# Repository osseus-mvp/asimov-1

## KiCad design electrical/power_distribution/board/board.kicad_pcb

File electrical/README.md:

## RPU 
> WIP

## Wiring

 was utilised for representing the wiring harness of the robot. 

Please refer to WireViz documentation for available visualisation options.
### Cable Naming Convention

```
W-<ID>-<TYPE>
ID = unique ID
TYPE = Power (PWR) or Signal (SIG) cable bundle
```

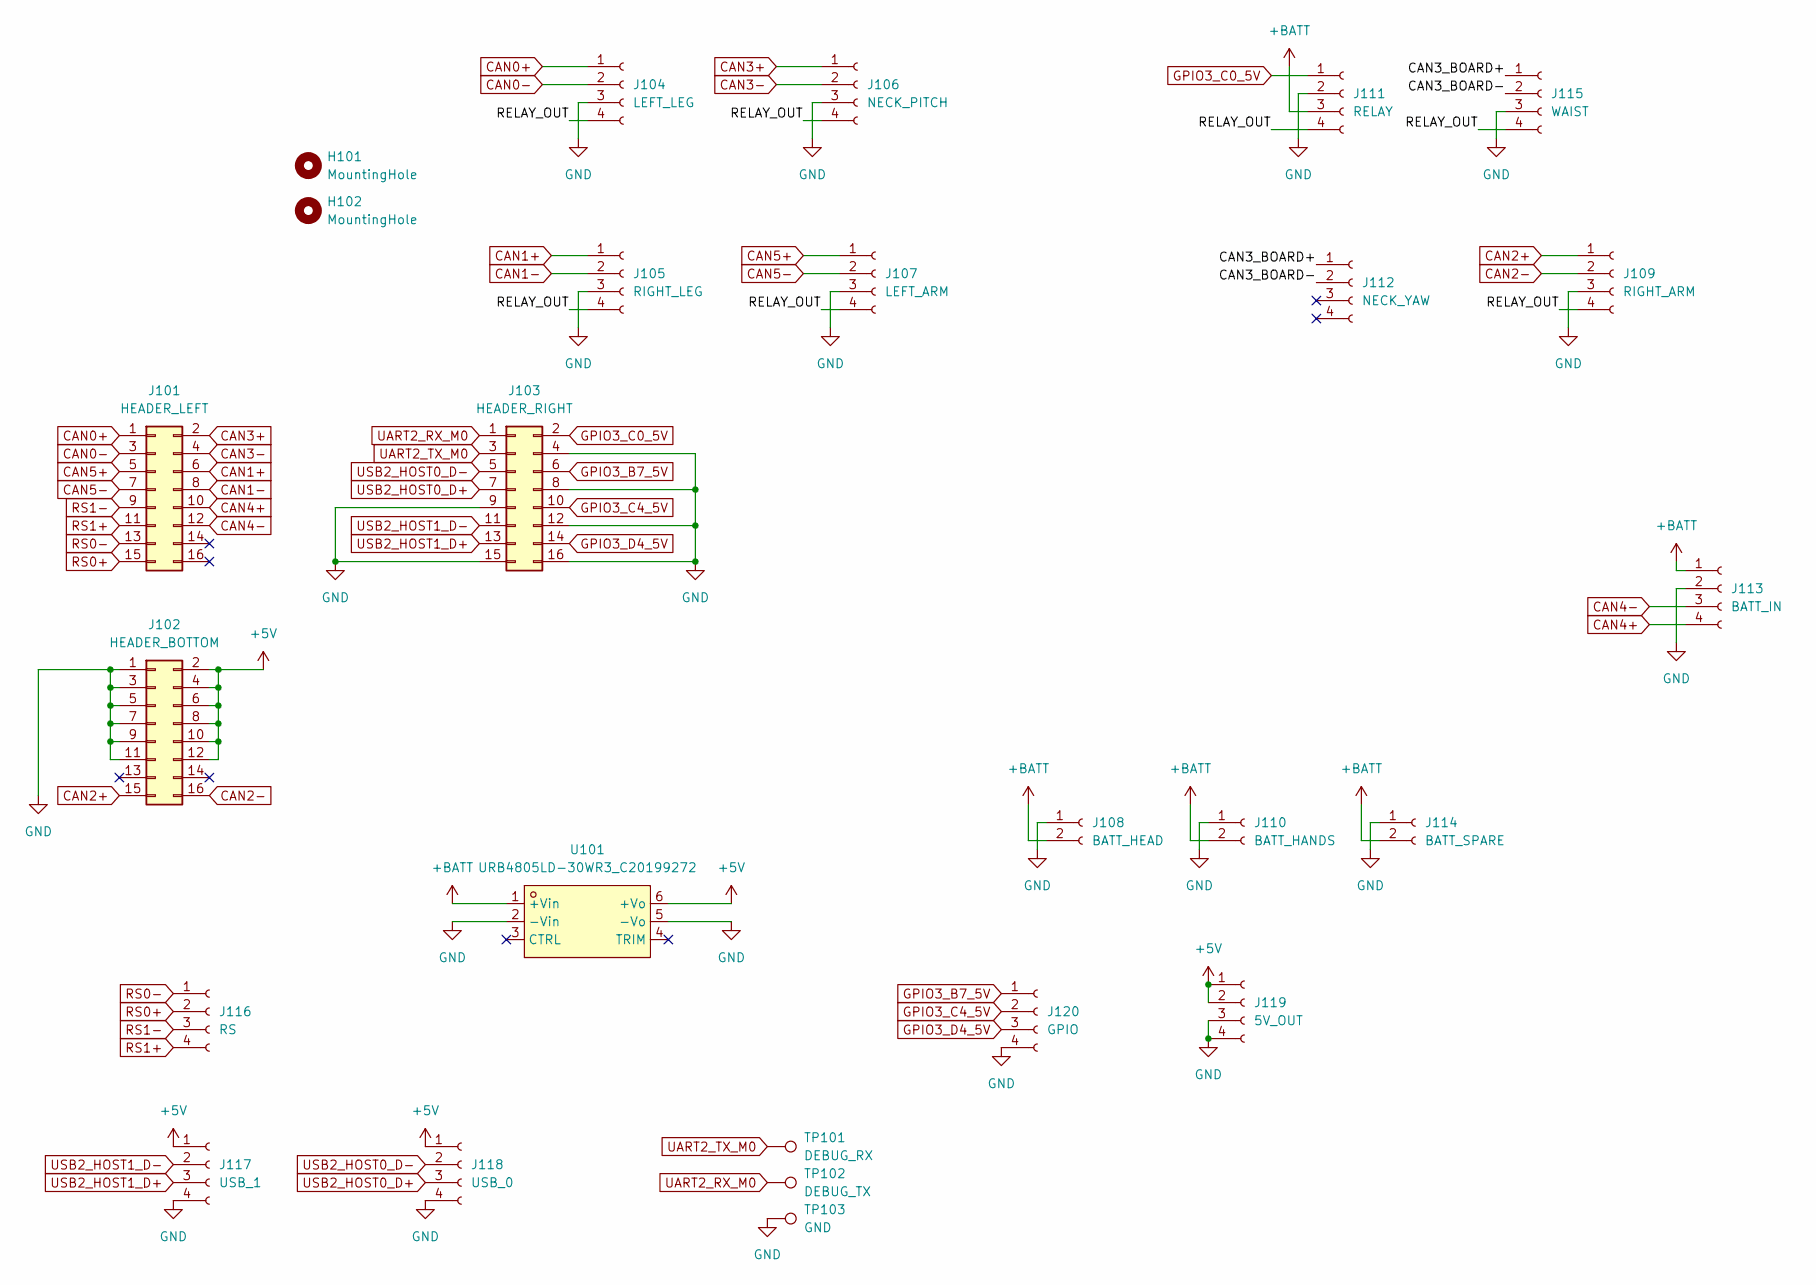
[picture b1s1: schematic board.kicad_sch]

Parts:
H101, H102: MountingHole; MountingHole_4.3mm_M4
J101: HEADER_LEFT; PinSocket_2x08_P2.54mm_Vertical; LCSC C30734
J102: HEADER_BOTTOM; PinSocket_2x08_P2.54mm_Vertical; LCSC C30734
J103: HEADER_RIGHT; PinSocket_2x08_P2.54mm_Vertical; LCSC C30734
J104: LEFT_LEG; CONN-TH_XT30PB-M
J105: RIGHT_LEG; CONN-TH_XT30PB-M
J106: NECK_PITCH; CONN-TH_XT30PB-M
J107: LEFT_ARM; CONN-TH_XT30PB-M
J108: BATT_HEAD; AMASS_XT30UPB-F_1x02_P5.0mm_Vertical; LCSC C108769
J109: RIGHT_ARM; CONN-TH_XT30PB-M
J110: BATT_HANDS; AMASS_XT30UPB-F_1x02_P5.0mm_Vertical; LCSC C108769
J111: RELAY; CONN-TH_XT30PB-M
J112: NECK_YAW; CONN-TH_XT30PB-M
J113: BATT_IN; CONN-SMD_XT90-2-2-PB-MGY; LCSC C19268046
J114: BATT_SPARE; AMASS_XT30UPB-F_1x02_P5.0mm_Vertical; LCSC C108769
J115: WAIST; CONN-TH_XT30PB-M
J116: RS; JST_XH_B4B-XH-A_1x04_P2.50mm_Vertical; LCSC C144395
J117: USB_1; JST_XH_B4B-XH-A_1x04_P2.50mm_Vertical; LCSC C144395
J118: USB_0; JST_XH_B4B-XH-A_1x04_P2.50mm_Vertical; LCSC C144395
J119: 5V_OUT; JST_XH_B4B-XH-A_1x04_P2.50mm_Vertical; LCSC C144395
J120: GPIO; JST_XH_B4B-XH-A_1x04_P2.50mm_Vertical; LCSC C144395
TP101: DEBUG_RX; TestPoint_Pad_D1.0mm
TP102: DEBUG_TX; TestPoint_Pad_D1.0mm
TP103: GND; TestPoint_Pad_D1.0mm
U101: URB4805LD-30WR3_C20199272; PWRM-TH_TURBXXXXLD-30WR3; MPN URB4805LD-30WR3; LCSC Part C20199272

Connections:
+5V: J102.2, J102.4, J102.6, J102.8, J102.10, J102.12, J117.1, J118.1, J119.1, J119.2, U101.6 (+Vo)
+BATT: J108.2, J110.2, J111.3, J113.1, J114.2, U101.1 (+Vin)
/CAN3_BOARD+: J112.1, J115.1
/CAN3_BOARD-: J112.2, J115.2
/RELAY_OUT: J104.4, J105.4, J106.4, J107.4, J109.4, J111.4, J115.4
CAN0+: J101.1, J104.1
CAN0-: J101.3, J104.2
CAN1+: J101.6, J105.1
CAN1-: J101.8, J105.2
CAN2+: J102.15, J109.1
CAN2-: J102.16, J109.2
CAN3+: J101.2, J106.1
CAN3-: J101.4, J106.2
CAN4+: J101.10, J113.4
CAN4-: J101.12, J113.3
CAN5+: J101.5, J107.1
CAN5-: J101.7, J107.2
GND: J102.1, J102.3, J102.5, J102.7, J102.9, J102.11, J103.4, J103.8, J103.9, J103.12, J103.15, J103.16, J104.3, J105.3, J106.3, J107.3, J108.1, J109.3, J110.1, J111.2, J113.2, J114.1, J115.3, J117.4, J118.4, J119.3, J119.4, J120.4, TP103.1 (1_1), U101.2 (-Vin), U101.5 (-Vo)
GPIO3_B7_5V: J103.6, J120.1
GPIO3_C0_5V: J103.2, J111.1
GPIO3_C4_5V: J103.10, J120.2
GPIO3_D4_5V: J103.14, J120.3
RS0+: J101.15, J116.2
RS0-: J101.13, J116.1
RS1+: J101.11, J116.4
RS1-: J101.9, J116.3
UART2_RX_M0: J103.1, TP102.1 (1_1)
UART2_TX_M0: J103.3, TP101.1 (1_1)
USB2_HOST0_D+: J103.7, J118.3
USB2_HOST0_D-: J103.5, J118.2
USB2_HOST1_D+: J103.13, J117.3
USB2_HOST1_D-: J103.11, J117.2

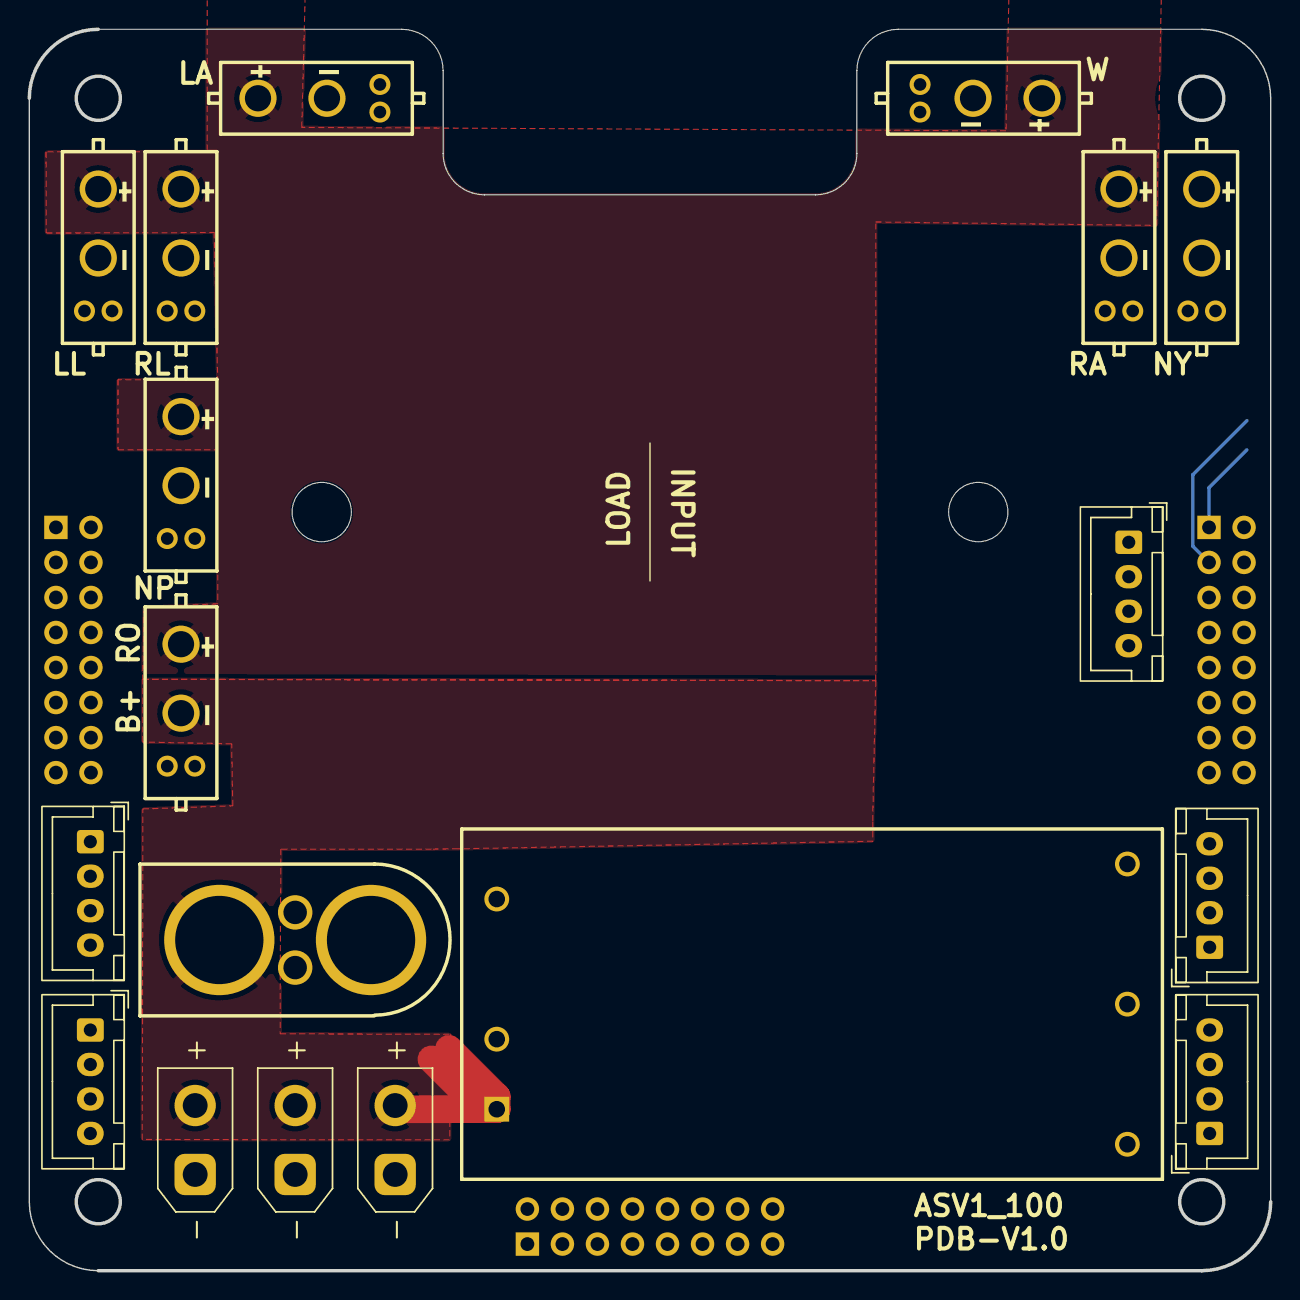
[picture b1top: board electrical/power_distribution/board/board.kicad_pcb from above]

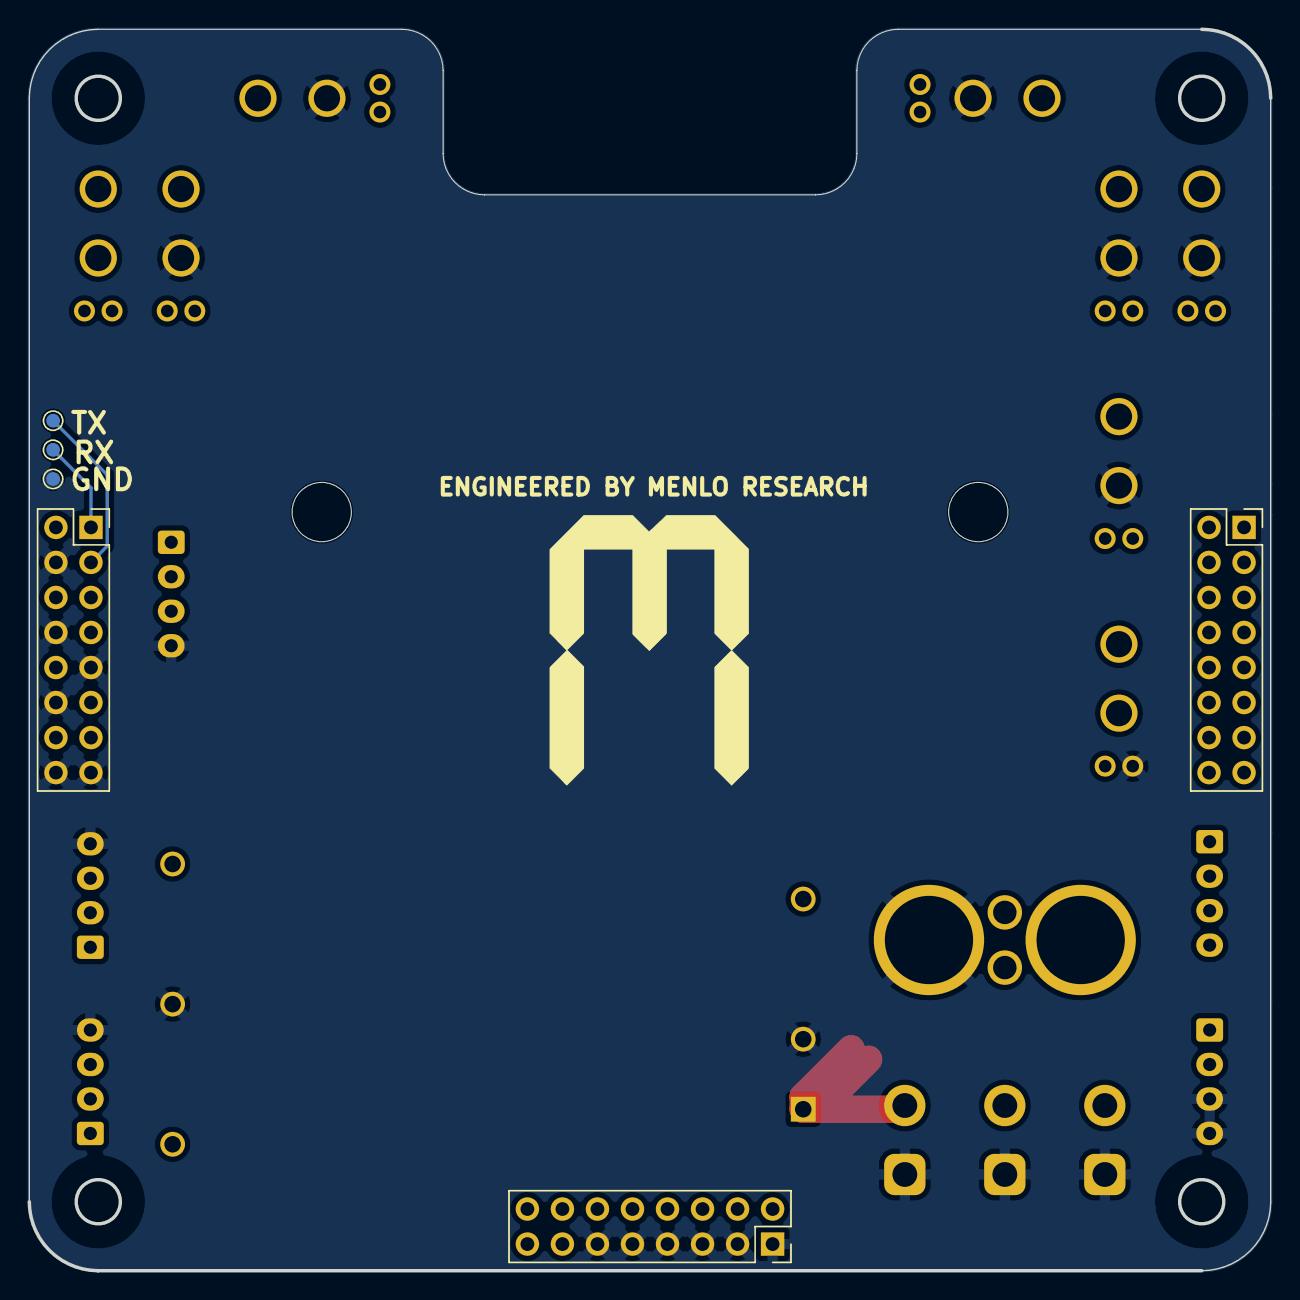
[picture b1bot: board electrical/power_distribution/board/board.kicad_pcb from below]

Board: 4 copper layers, 90.0 x 90.0 mm, 26 parts (6 on the bottom side), 32 nets.

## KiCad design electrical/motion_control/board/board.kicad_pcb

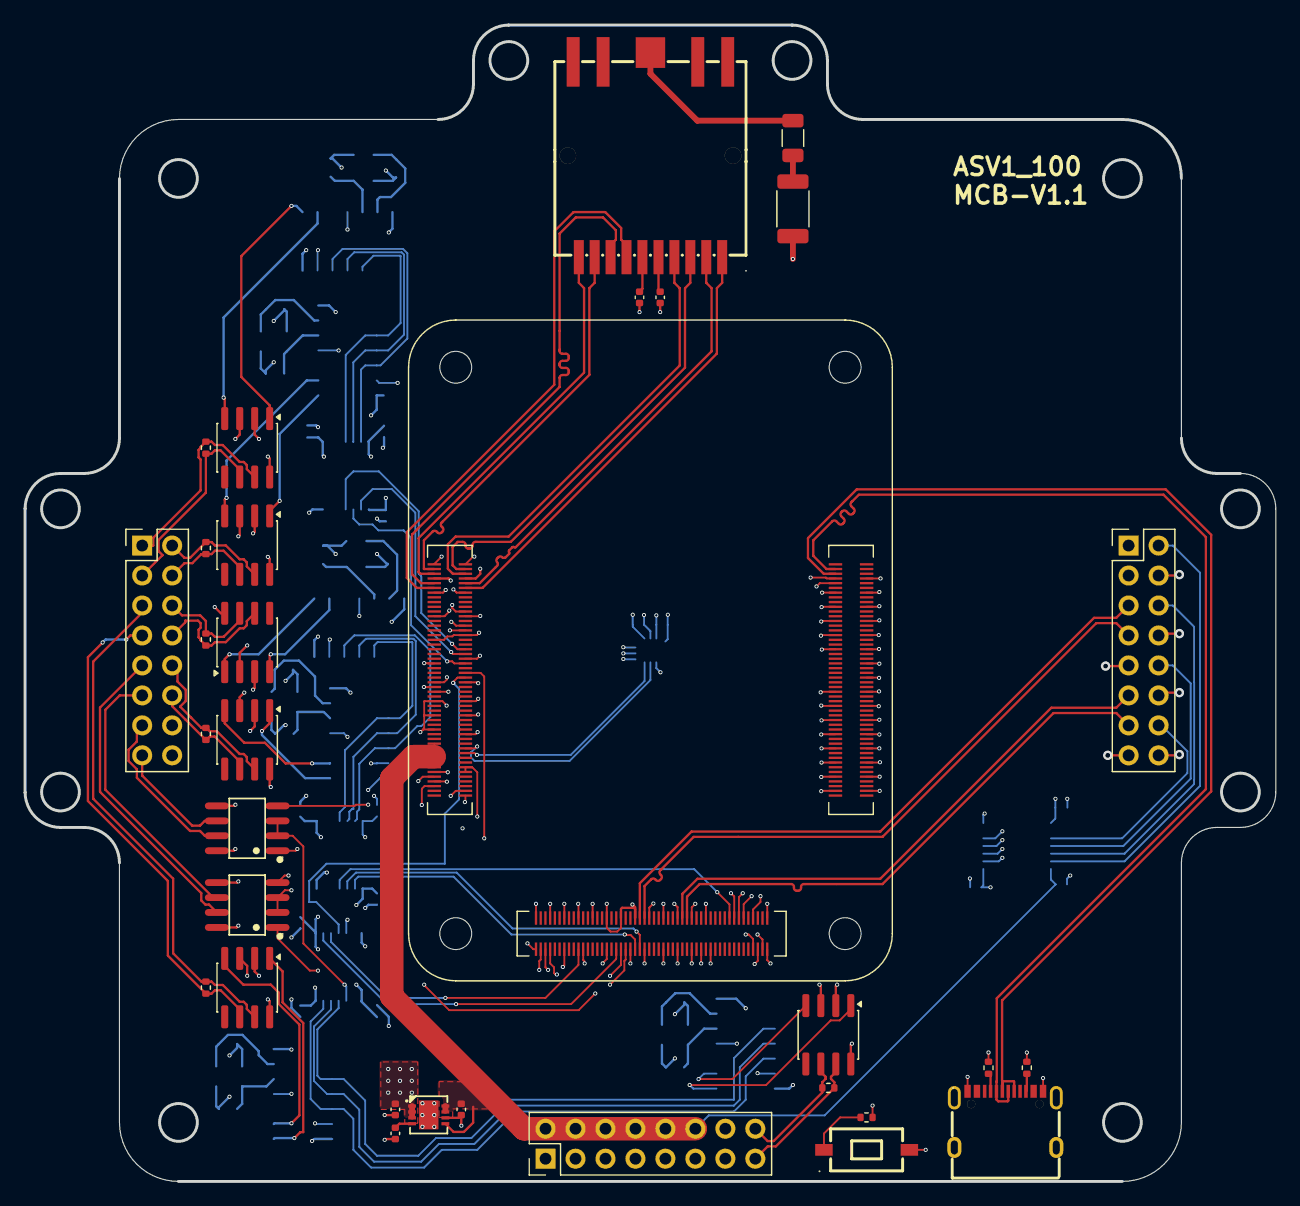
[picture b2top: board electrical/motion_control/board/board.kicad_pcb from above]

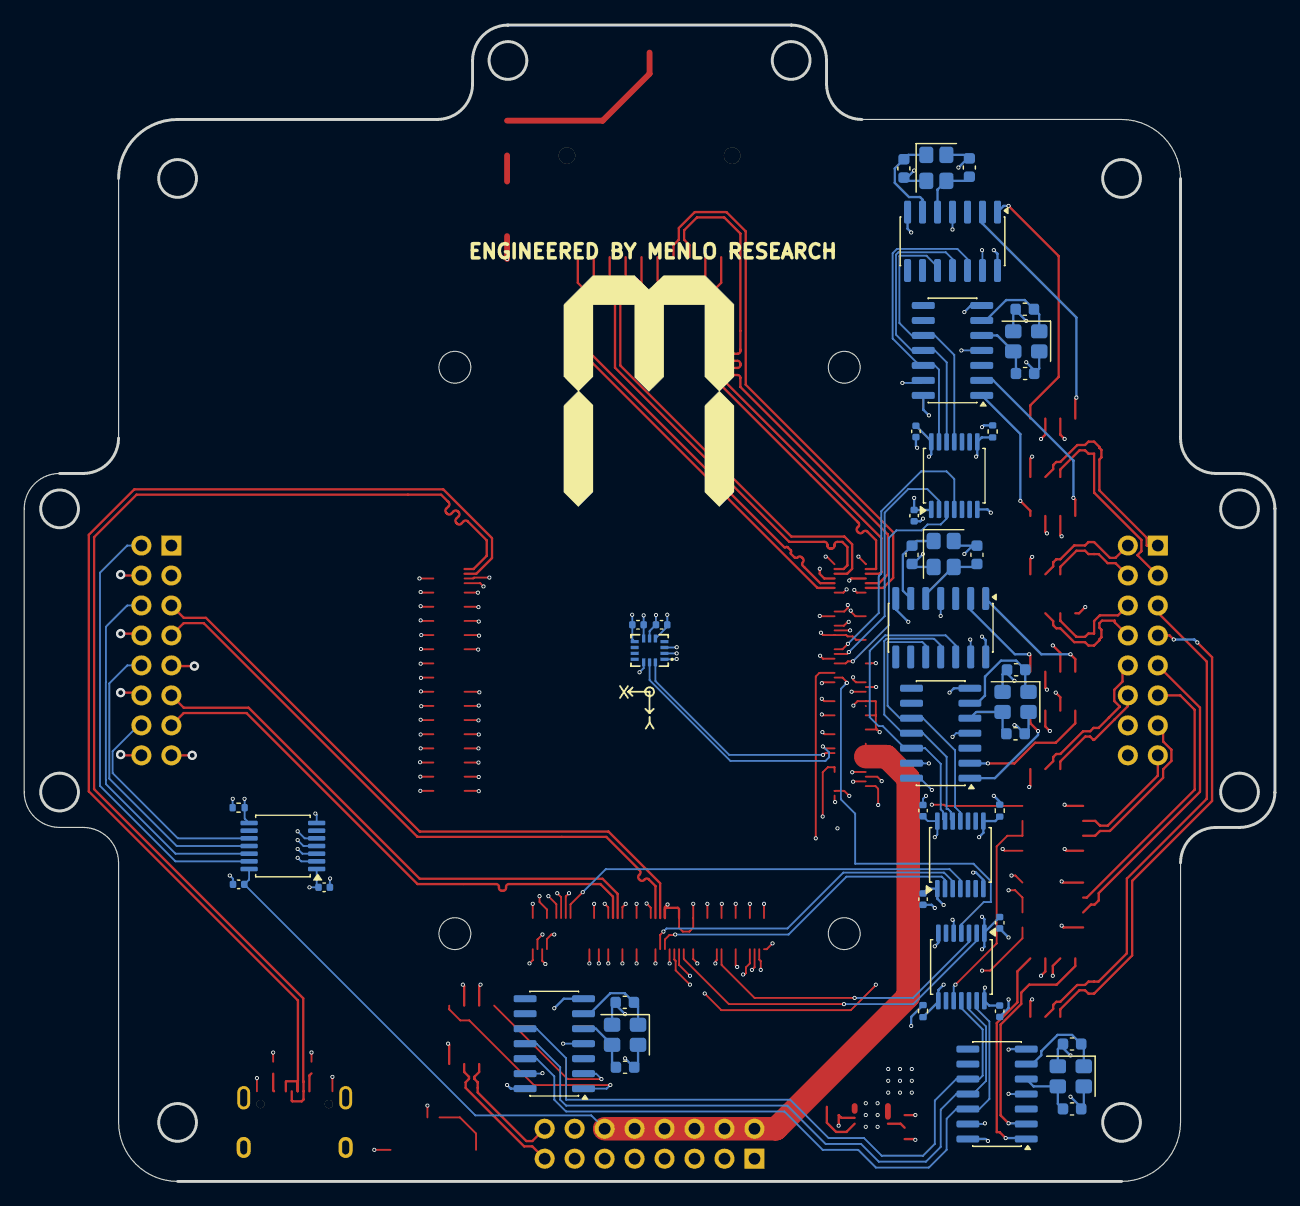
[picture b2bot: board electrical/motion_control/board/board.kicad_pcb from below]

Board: 4 copper layers, 106.0 x 98.0 mm, 77 parts (43 on the bottom side), 116 nets.

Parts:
C101, C103: 4.7u; C_0402_1005Metric
C102: 1n; C_0402_1005Metric
C201, C202, C204, C205, C501, C502, C503, C504, C505, C506, C507, C508: 100n; C_0402_1005Metric
C203: 1n; C_1206_3216Metric
C601, C602, C603, C604, C605, C606, C607, C608, C609, C610, C611, C612: 20p; C_0603_1608Metric
J101: HEADER_LEFT; PinHeader_2x08_P2.54mm_Vertical
J102: HEADER_BOTTOM; PinHeader_2x08_P2.54mm_Vertical
J103: HEADER_RIGHT; PinHeader_2x08_P2.54mm_Vertical
R201: 1M; R_2010_5025Metric
R202: 100; R_0402_1005Metric
R301, R302: 5.1k; R_0402_1005Metric
R501, R502, R503, R504: 10k; R_0402_1005Metric
R601, R602, R603, R604, R605, R606: 120; R_0402_1005Metric
SW201: TS50810-411-02528; SW-SMD_L6.2-W3.7-LS8.0
U101: ADM7172ACPZ-3.3-R7; DFN-8_L3.0-W3.0-P0.50-BL-EP
U201: Hirose DF40C-100DS-0.4V; radxa_cm5_1
U202: ETH; RJ45-SMD_HR963380AE
U203: LSM6DSVTR; LGA-14_L3.0-W2.5-P0.50-TL
U301: Hirose DF40C-100DS-0.4V; radxa_cm5_2
U401: Hirose DF40C-100DS-0.4V; radxa_cm5_3
U501, U502, U503, U504: TXB0104PW; TSSOP-14_4.4x5mm_P0.65mm
U601, U602, U603, U607, U608, U609: MCP2518FD-xQBB; SOIC-14_3.9x8.7mm_P1.27mm
U604, U605, U606, U610, U611, U612: SN65HVD230; SOIC-8_3.9x4.9mm_P1.27mm
U701, U702: SN65HVD10DR; SOIC-8_L4.9-W3.9-P1.27-LS6.0-BL
USB301: TYPE-C 16PIN 2MD; USB-C-SMD_TYPE-C-16PIN-2MD-073
Y601, Y602, Y603, Y604, Y605, Y606: 40M; Crystal_SMD_3225-4Pin_3.2x2.5mm

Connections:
+1V8: C503.1, C505.1, C506.1, R502.2, R503.2, R504.2, U201.88 (+1.8v_(Output)), U201.90 (+1.8v_(Output)), U502.1 (VCCA), U502.8 (OE), U503.1 (VCCA), U503.8 (OE), U504.1 (VCCA), U504.8 (OE)
+3V3: C101.1, C201.1, C202.1, C501.1, C504.1, C507.1, C508.1, R501.2, U101.1 (OUT), U101.2 (OUT), U101.3 (SENSE), U203.5 (VDD_IO), U203.8 (VDD), U203.12 (CS), U501.1 (VCCA), U501.8 (OE), U502.14 (VCCB), U503.14 (VCCB), U504.14 (VCCB), U601.14 (VDD), U602.14 (VDD), U603.14 (VDD), U604.3 (VCC), U605.3 (VCC), U606.3 (VCC), U607.14 (VDD), U608.14 (VDD), U609.14 (VDD), U610.3 (VCC), U611.3 (VCC), U612.3 (VCC), U701.8 (VCC), U702.8 (VCC)
+5V: C103.1, C502.1, J102.2, J102.4, J102.6, J102.8, J102.10, J102.12, U101.5 (EN), U101.7 (VIN), U101.8 (VIN), U201.77 (+5v_(Input)), U201.79 (+5v_(Input)), U201.81 (+5v_(Input)), U201.83 (+5v_(Input)), U201.85 (+5v_(Input)), U201.87 (+5v_(Input)), U501.14 (VCCB)
/J1/GPIO3_B7_3V3: U401.206 (GPIO_3V3_2), U501.3 (A2)
/J1/GPIO3_C0_3V3: U401.204 (GPIO_3V3_1), U501.2 (A1)
/J1/GPIO3_C4_3V3: U401.208 (GPIO_3V3_3), U501.4 (A3)
/J1/GPIO3_D4_3V3: U401.214 (GPIO_3V3_4), U501.5 (A4)
/J1/SPI1_CLK_M2_1V8: U401.283 (GPIO_1V8_12), U503.4 (A3)
/J1/SPI1_CS0: U401.238 (GPIO_3V3_7), U603.13 (~CS)
/J1/SPI1_CS1: U401.294 (GPIO_3V3_9), U608.13 (~CS)
/J1/SPI1_INT0: U401.240 (GPIO_3V3_8), U603.4 (~INT)
/J1/SPI1_INT1: U401.298 (GPIO_3V3_BT_REG_ON), U608.4 (~INT)
/J1/SPI1_MISO_M2_1V8: U401.244 (GPIO_1V8_6), U503.2 (A1)
/J1/SPI1_MOSI_M2_1V8: U401.246 (GPIO_1V8_7), U503.3 (A2)
/J1/SPI4_CS0: U401.287 (GPIO_3V3_13), U601.13 (~CS)
/J1/SPI4_CS1: U401.293 (GPIO_3V3_15), U609.13 (~CS)
/J1/SPI4_INT0: U401.285 (GPIO_3V3_12), U601.4 (~INT)
/J1/SPI4_INT1: U401.289 (GPIO_3V3_14), U609.4 (~INT)
/J1/SPI4_MISO_M0_1V8: U401.236 (GPIO_1V8_HP_DET_L), U504.2 (A1)
/J1/SPI4_MOSI_M0_1V8: U401.220 (GPIO_1V8_3), U504.3 (A2)
/J1/UART0_RX_M0: U401.296 (GPIO_3V3_CC_INT0_L), U702.1 (R)
/RS485/UART0_RTSN: U201.91 (BT_nDisable), U702.2 (~RE), U702.3 (DE)
/RS485/UART0_TX_M0: U201.89 (WiFi_nDisable), U702.4 (D)
/RS485/UART4_RTSN: U504.10 (B4), U701.2 (~RE), U701.3 (DE)
/RS485/UART4_RX_M1: U201.24 (GPIO26), U701.1 (R)
/RS485/UART4_TX_M1: U301.109 (PCIe_nRST), U701.4 (D)
/SPI-CAN/SPI0_CLK: U502.11 (B3), U602.10 (SCK), U607.10 (SCK)
/SPI-CAN/SPI0_CS0: U201.95 (nPI_LED_PWR), U602.13 (~CS)
/SPI-CAN/SPI0_CS1: U201.100 (nEXTRST), U607.13 (~CS)
/SPI-CAN/SPI0_INT0: U201.30 (GPIO6), U602.4 (~INT)
/SPI-CAN/SPI0_INT1: U201.28 (GPIO13), U607.4 (~INT)
/SPI-CAN/SPI00_OSC_1: C602.1, U602.6 (OSC1), Y602.1
/SPI-CAN/SPI00_OSC_2: C605.1, U602.5 (OSC2), Y602.3
/SPI-CAN/SPI0_SI: U502.12 (B2), U602.11 (SDI), U607.11 (SDI)
/SPI-CAN/SPI0_SO: U502.13 (B1), U602.12 (SDO), U607.12 (SDO)
/SPI-CAN/SPI1_CLK: U503.11 (B3), U603.10 (SCK), U608.10 (SCK)
/SPI-CAN/SPI01_OSC_1: C607.1, U607.6 (OSC1), Y604.1
/SPI-CAN/SPI01_OSC_2: C610.1, U607.5 (OSC2), Y604.3
/SPI-CAN/SPI1_SI: U503.12 (B2), U603.11 (SDI), U608.11 (SDI)
/SPI-CAN/SPI1_SO: U503.13 (B1), U603.12 (SDO), U608.12 (SDO)
/SPI-CAN/SPI4_CLK: U504.11 (B3), U601.10 (SCK), U609.10 (SCK)
/SPI-CAN/SPI4_SI: U504.12 (B2), U601.11 (SDI), U609.11 (SDI)
/SPI-CAN/SPI4_SO: U504.13 (B1), U601.12 (SDO), U609.12 (SDO)
/SPI-CAN/SPI10_OSC_1: C603.1, U603.6 (OSC1), Y603.1
/SPI-CAN/SPI10_OSC_2: C606.1, U603.5 (OSC2), Y603.3
/SPI-CAN/SPI11_OSC_1: C608.1, U608.6 (OSC1), Y605.1
/SPI-CAN/SPI11_OSC_2: C611.1, U608.5 (OSC2), Y605.3
/SPI-CAN/SPI40_OSC_1: C601.1, U601.6 (OSC1), Y601.1
/SPI-CAN/SPI40_OSC_2: C604.1, U601.5 (OSC2), Y601.3
/SPI-CAN/SPI41_OSC_1: C609.1, U609.6 (OSC1), Y606.1
/SPI-CAN/SPI41_OSC_2: C612.1, U609.5 (OSC2), Y606.3
/TTL-SHIFT/SPI0_CLK_M2_1V8: U201.38 (GPIO11), U502.4 (A3)
/TTL-SHIFT/SPI0_MISO_M2_1V8: U201.40 (GPIO9), U502.2 (A1)
/TTL-SHIFT/SPI0_MOSI_M2_1V8: U201.44 (GPIO10), U502.3 (A2)
/TTL-SHIFT/SPI4_CLK_M0_1V8: U201.50 (GPIO17), U504.4 (A3)
/TTL-SHIFT/UART4_RTSN_1V8: U201.48 (GPIO27), U504.5 (A4)
/U13A/CT0: C204.1, U202.5
/U13A/CT1: C205.1, U202.6
/U13A/Ethernet_Pair0_N: U201.10 (Ethernet_Pair0_N), U202.2
/U13A/Ethernet_Pair0_P: U201.12 (Ethernet_Pair0_P), U202.1
/U13A/Ethernet_Pair1_N: U201.6 (Ethernet_Pair1_N), U202.4
/U13A/Ethernet_Pair1_P: U201.4 (Ethernet_Pair1_P), U202.3
/U13A/Ethernet_Pair2_N: U201.9 (Ethernet_Pair2_N), U202.8
/U13A/Ethernet_Pair2_P: U201.11 (Ethernet_Pair2_P), U202.7
/U13A/Ethernet_Pair3_N: U201.5 (Ethernet_Pair3_N), U202.10
/U13A/Ethernet_Pair3_P: U201.3 (Ethernet_Pair3_P), U202.9
/U13A/IMU_I2C7_SCL_M2: U201.80 (SCL0), U203.13 (SCL)
/U13A/IMU_I2C7_SDA_M2: U201.82 (SDA0), U203.14 (SDA)
/U13A/MASKROM_KEY: R202.1, U201.93 (nRPIBOOT)
/U13B/USB2_D+: U301.105 (USB2_P), USB301.A6 (Dp1), USB301.B6 (Dp2)
/U13B/USB2_D-: U301.103 (USB2_N), USB301.A7 (Dn1), USB301.B7 (Dn2)
CAN0+: J101.1, R604.1, U610.7 (CANH)
CAN0-: J101.3, R604.2, U610.6 (CANL)
CAN1+: J101.6, R605.1, U611.7 (CANH)
CAN1-: J101.8, R605.2, U611.6 (CANL)
CAN2+: J102.15, R606.1, U612.7 (CANH)
CAN2-: J102.16, R606.2, U612.6 (CANL)
CAN3+: J101.2, R602.1, U605.7 (CANH)
CAN3-: J101.4, R602.2, U605.6 (CANL)
CAN4+: J101.10, R603.1, U606.7 (CANH)
CAN4-: J101.12, R603.2, U606.6 (CANL)
CAN5+: J101.5, R601.1, U604.7 (CANH)
CAN5-: J101.7, R601.2, U604.6 (CANL)
Earth: C203.2, U202.15
GND: C101.2, C102.2, C103.2, C201.2, C202.2, C204.2, C205.2, C501.2, C502.2, C503.2, C504.2, C505.2, C506.2, C507.2, C508.2, C601.2, C602.2, C603.2, C604.2, C605.2, C606.2, C607.2, C608.2, C609.2, C610.2, C611.2, C612.2, J102.1, J102.3, J102.5, J102.7, J102.9, J102.11, J103.4, J103.8, J103.9, J103.12, J103.15, J103.16, R201.1, R301.1, R302.1, R501.1, R502.1, R503.1, R504.1, SW201.2, U101.6 (GND), U101.9 (EP), U201.1 (GND), U201.2 (GND), U201.7 (GND), U201.8 (GND), U201.13 (GND), U201.14 (GND), U201.22 (GND), U201.23 (GND), U201.32 (GND), U201.33 (GND), U201.42 (GND), U201.43 (GND), U201.52 (GND), U201.53 (GND), U201.59 (GND), U201.60 (GND), U201.65 (GND), U201.66 (GND), U201.71 (GND), U201.74 (GND), U201.98 (GND), U203.1 (SDO/SA0), U203.2 (SDX), U203.3 (SCX), U203.6 (GND), U203.7 (GND), U301.107 (GND), U301.108 (GND), U301.113 (GND), U301.114 (GND), U301.119 (GND), U301.120 (GND), U301.125 (GND), U301.126 (GND), U301.131 (GND), U301.132 (GND), U301.137 (GND), U301.138 (GND), U301.144 (GND), U301.150 (GND), U301.155 (GND), U301.156 (GND), U301.161 (GND), U301.162 (GND), U301.167 (GND), U301.168 (GND), U301.173 (GND), U301.174 (GND), U301.179 (GND), U301.180 (GND), U301.185 (GND), U301.186 (GND), U301.191 (GND), U301.192 (GND), U301.197 (GND), U301.198 (GND), U401.201 (GND), U401.202 (GND), U401.207 (GND), U401.213 (GND), U401.219 (GND), U401.222 (GND), U401.225 (GND), U401.231 (GND), U401.232 (GND), U401.237 (GND), U401.242 (GND), U401.243 (GND), U401.248 (GND), U401.249 (GND), U401.255 (GND), U401.256 (GND), U401.261 (GND), U401.262 (GND), U401.267 (GND), U401.268 (GND), U401.272 (GND), U401.273 (GND), U401.276 (GND), U401.299 (GND), U401.300 (GND), U501.7 (GND), U502.7 (GND), U503.7 (GND), U504.7 (GND), U601.7 (VSS), U602.7 (VSS), U603.7 (VSS), U604.2 (GND), U604.8 (Rs), U605.2 (GND), U605.8 (Rs), U606.2 (GND), U606.8 (Rs), U607.7 (VSS), U608.7 (VSS), U609.7 (VSS), U610.2 (GND), U610.8 (Rs), U611.2 (GND), U611.8 (Rs), U612.2 (GND), U612.8 (Rs), U701.5 (GND), U702.5 (GND), USB301.A1B12 (GND), USB301.B1A12 (GND), Y601.2, Y601.4, Y602.2, Y602.4, Y603.2, Y603.4, Y604.2, Y604.4, Y605.2, Y605.4, Y606.2, Y606.4
GPIO3_B7_5V: J103.6, U501.12 (B2)
GPIO3_C0_5V: J103.2, U501.13 (B1)
GPIO3_C4_5V: J103.10, U501.11 (B3)
GPIO3_D4_5V: J103.14, U501.10 (B4)
unnamed: C203.1, R201.2
unnamed: R202.2, SW201.1
unnamed: C102.1, U101.4 (SS)
unnamed: U601.2 (RXCAN), U604.4 (R)
unnamed: U601.1 (TXCAN), U604.1 (D)
unnamed: U602.2 (RXCAN), U605.4 (R)
unnamed: U602.1 (TXCAN), U605.1 (D)
unnamed: U603.2 (RXCAN), U606.4 (R)
unnamed: U603.1 (TXCAN), U606.1 (D)
unnamed: U607.2 (RXCAN), U610.4 (R)
unnamed: U607.1 (TXCAN), U610.1 (D)
unnamed: U608.2 (RXCAN), U611.4 (R)
unnamed: U608.1 (TXCAN), U611.1 (D)
unnamed: U609.2 (RXCAN), U612.4 (R)
unnamed: U609.1 (TXCAN), U612.1 (D)
unnamed: R301.2, USB301.A5 (CC1)
unnamed: R302.2, USB301.B5 (CC2)
RS0+: J101.15, U701.6 (A)
RS0-: J101.13, U701.7 (B)
RS1+: J101.11, U702.6 (A)
RS1-: J101.9, U702.7 (B)
UART2_RX_M0: J103.1, U201.51 (GPIO15)
UART2_TX_M0: J103.3, U201.55 (GPIO14)
USB2_HOST0_D+: J103.7, U401.247 (USB3_HOST1_DM)
USB2_HOST0_D-: J103.5, U401.245 (USB3_HOST1_DP)
USB2_HOST1_D+: J103.13, U401.265 (USB2_HOST2_DM)
USB2_HOST1_D-: J103.11, U401.263 (USB2_HOST2_DP)
